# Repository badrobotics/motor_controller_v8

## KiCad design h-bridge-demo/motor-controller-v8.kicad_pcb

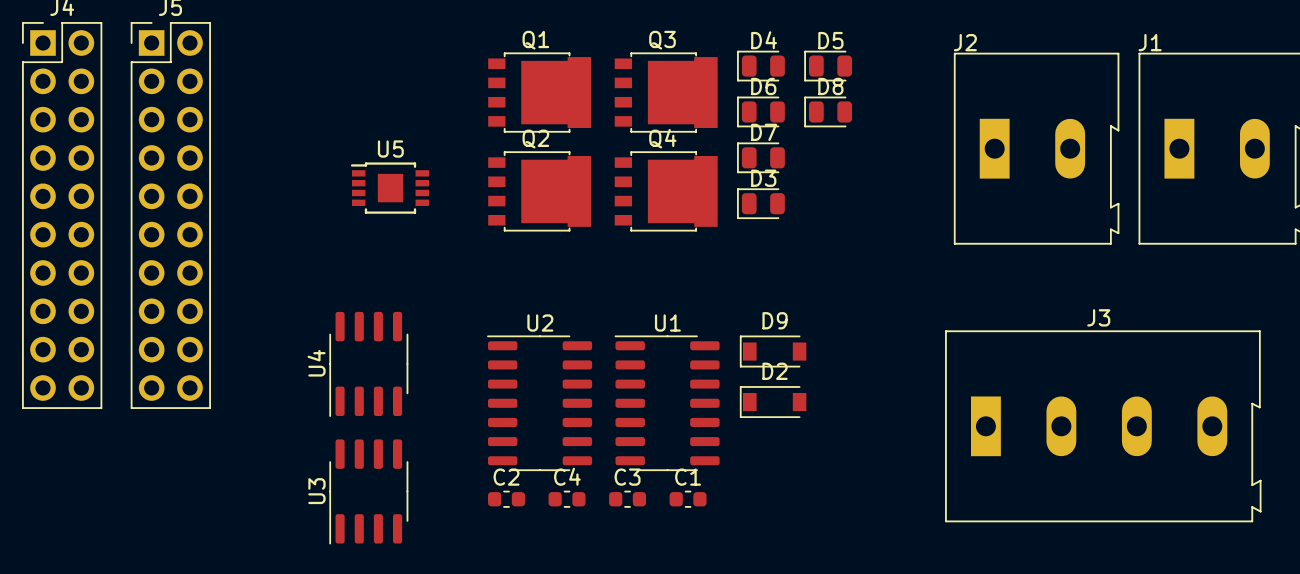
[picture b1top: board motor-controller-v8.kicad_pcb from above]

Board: 2 copper layers, 26 parts (0 on the bottom side), 18 nets, no tracks yet.

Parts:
C1, C2: 10u; C_0603_1608Metric
C3, C4: 1u; C_0603_1608Metric
D2, D9: 1N4148W; D_SOD-123
D3, D4, D5, D6, D7, D8: D_TVS; D_0805_2012Metric
J1, J2: Conn_01x02; TerminalBlock_Altech_AK300-2_P5.00mm
J3: Conn_01x04; TerminalBlock_Altech_AK300-4_P5.00mm
J4, J5: Conn_02x10_Counter_Clockwise; PinHeader_2x10_P2.54mm_Vertical
Q1, Q2, Q3, Q4: PSMN5R2-60YL; LFPAK56
U1, U2: LT1160; SOIC-14_3.9x8.7mm_P1.27mm
U3, U4: ADuM120N; SOIC-8_3.9x4.9mm_P1.27mm
U5: LT3010-5; MSOP-8-1EP_3x3mm_P0.65mm_EP1.68x1.88mm

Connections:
+5V: U3.8, U4.8, U5.1, U5.2
+BATT: C1.1, C2.1, D2.2, D9.2, J1.2, Q1.5, Q3.5, U1.1, U1.10, U2.1, U2.10, U5.5, U5.8
/GND_launchpad: U3.4, U4.4
/Vin_launchpad: U3.1, U4.1
/motor_driver_0/IN_BOTTOM_0: U1.3, U3.6
/motor_driver_0/IN_BOTTOM_1: U2.3, U4.6
/motor_driver_0/IN_TOP_0: U1.2, U3.7
/motor_driver_0/IN_TOP_1: U2.2, U4.7
/motor_driver_0/MOTOR+: D3.2, D5.1, J2.1, Q1.1, Q1.2, Q1.3, Q2.5
/motor_driver_0/MOTOR-: D6.1, D7.2, J2.2, Q3.1, Q3.2, Q3.3, Q4.5
/motor_driver_0/sheet5E6D395B/GHA1: D3.1, D4.1, Q1.4, Q2.4, U1.8, U1.9, U1.12, U1.13
/motor_driver_0/sheet5E6D395B/GHA2: D7.1, D8.1, Q3.4, Q4.4, U2.8, U2.9, U2.12, U2.13
GND: C1.2, C2.2, J1.1, U1.5, U2.5, U3.5, U4.5, U5.4, U5.9
GNDPWR: D4.2, D5.2, D6.2, D8.2, Q2.1, Q2.2, Q2.3, Q4.1, Q4.2, Q4.3, U1.6, U2.6
unnamed: C3.1, D2.1, U1.14
unnamed: C3.2, U1.11
unnamed: C4.1, D9.1, U2.14
unnamed: C4.2, U2.11

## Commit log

2019-07-03 Create LICENSE
2020-03-14 basic h-bridge schematic
2020-03-14 removing backup and cache files
2020-03-14 adding pwm isolation
